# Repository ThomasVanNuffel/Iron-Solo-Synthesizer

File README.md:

# Main Directory
This repository is about the two phases of the project.

First phase: Practise Enterprise 1

    - XC888-DIL (microcontroller)
    - Input matrix with keys from keyboard
    - Led matrix
    - Serial interface with signal generators (with chip selector)

Second phase: Practise Enterprise 2

    - STM32F7508-DK (microcontroller)
    - Better serial interface with more signal generators
    - Communication with XC888 (to have all features of previous year)
    - MIDI communication
    - Hardware audio effects:
        - Envelopes
        - Low pass filter
        - High pas filter

    - Line input with small mixing stage

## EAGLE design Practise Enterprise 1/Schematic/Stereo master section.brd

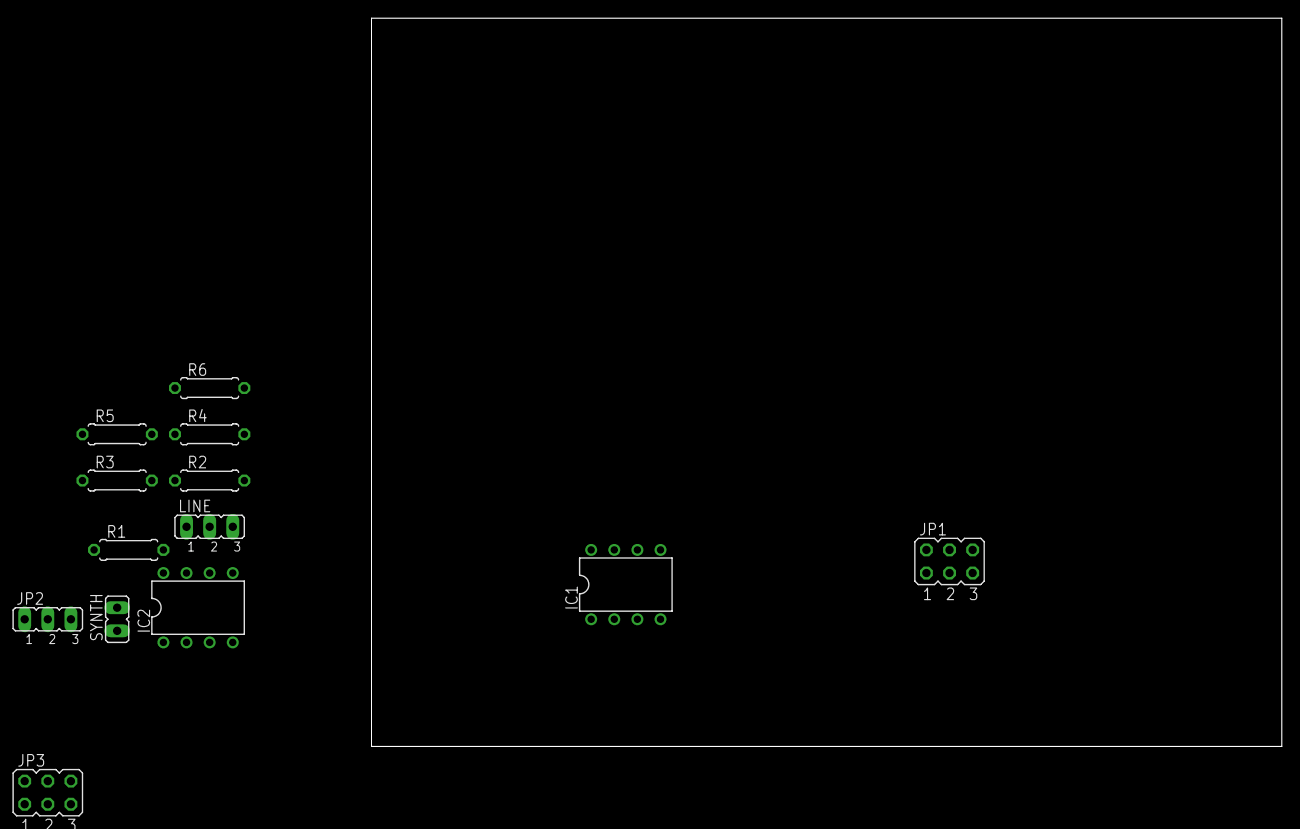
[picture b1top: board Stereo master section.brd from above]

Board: 2 copper layers, 100.0 x 80.0 mm, 13 parts (0 on the bottom side), 13 nets, no tracks yet.

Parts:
IC1, IC2: LM358N; DIL08
JP1, JP3: JP3Q
JP2: JP2
LINE: JP2
R1, R2, R5, R6: 1k; 0207/7
R3, R4: 5k; 0207/7
SYNTH: JP1

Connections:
unnamed: R3.1, R4.1, SYNTH.2
unnamed: IC1.2, R1.1, R3.2
unnamed: IC2.6, JP1.3, R5.2
unnamed: IC1.6, R2.1, R4.2
unnamed: IC1.7, LINE.2, R2.2, R5.1
unnamed: IC2.2, JP1.4, R6.2
unnamed: LINE.3, R6.1
unnamed: IC2.7, JP1.5
unnamed: IC2.1, JP1.6
unnamed: IC1.8, IC2.8, JP2.3
unnamed: IC1.4, IC2.4, JP2.2
unnamed: IC1.3, IC1.5, IC2.3, IC2.5, JP1.1, JP1.2, JP2.1, SYNTH.1
unnamed: IC1.1, R1.2

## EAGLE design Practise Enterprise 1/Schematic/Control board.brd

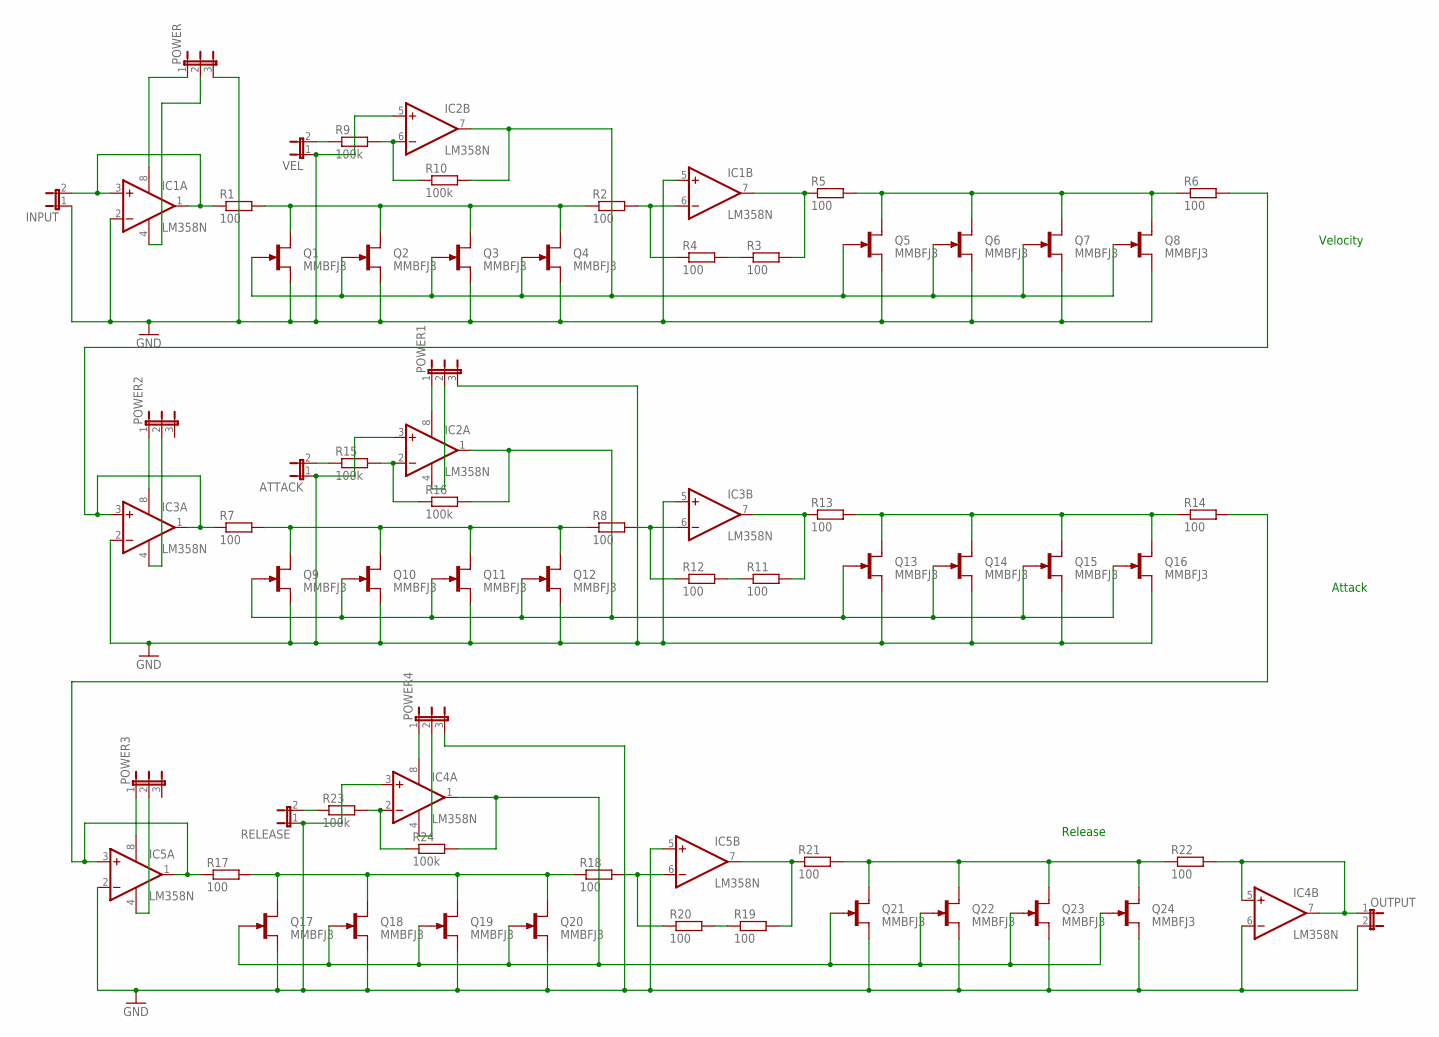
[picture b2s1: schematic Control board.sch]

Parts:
ATTACK: JP1E; JP1
IC1, IC2, IC3, IC4, IC5: LM358N; DIL08
INPUT: JP1E; JP1
OUTPUT: JP1E; JP1
POWER, POWER1, POWER2, POWER3, POWER4: JP2E; JP2
Q1, Q2, Q3, Q4, Q5, Q6, Q7, Q8, Q9, Q10, Q11, Q12, Q13, Q14, Q15, Q16, Q17, Q18, Q19, Q20, Q21, Q22, Q23, Q24: MMBFJ3; SOT23
R1, R2, R3, R4, R5, R6, R7, R8, R11, R12, R13, R14, R17, R18, R19, R20, R21, R22: 100; 0204/7
R9, R10, R15, R16, R23, R24: 100k; 0204/7
RELEASE: JP1E; JP1
VEL: JP1E; JP1

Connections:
22: Q13.1 (D), Q14.1 (D), Q15.1 (D), Q16.1 (D), R13.2, R14.1
CONTROL: IC2.7 (OUT), Q1.3 (G), Q2.3 (G), Q3.3 (G), Q4.3 (G), Q5.3 (G), Q6.3 (G), Q7.3 (G), Q8.3 (G), R10.2
CONTROL1: IC2.1 (OUT), Q9.3 (G), Q10.3 (G), Q11.3 (G), Q12.3 (G), Q13.3 (G), Q14.3 (G), Q15.3 (G), Q16.3 (G), R16.2
CONTROL2: IC4.1 (OUT), Q17.3 (G), Q18.3 (G), Q19.3 (G), Q20.3 (G), Q21.3 (G), Q22.3 (G), Q23.3 (G), Q24.3 (G), R24.2
GND: ATTACK.1, IC1.2 (-IN), IC1.5 (+IN), IC2.3 (+IN), IC2.5 (+IN), IC3.2 (-IN), IC3.5 (+IN), IC4.3 (+IN), IC4.6 (-IN), IC5.2 (-IN), IC5.5 (+IN), INPUT.1, OUTPUT.2, POWER.3, POWER1.3, POWER4.3, Q1.2 (S), Q2.2 (S), Q3.2 (S), Q4.2 (S), Q5.2 (S), Q6.2 (S), Q7.2 (S), Q8.2 (S), Q9.2 (S), Q10.2 (S), Q11.2 (S), Q12.2 (S), Q13.2 (S), Q14.2 (S), Q15.2 (S), Q16.2 (S), Q17.2 (S), Q18.2 (S), Q19.2 (S), Q20.2 (S), Q21.2 (S), Q22.2 (S), Q23.2 (S), Q24.2 (S), RELEASE.1, VEL.1
unnamed: IC4.8 (V+), POWER4.1
unnamed: IC1.8 (V+), POWER.1
unnamed: IC1.6 (-IN), R2.2, R4.1
unnamed: IC1.1 (OUT), IC1.3 (+IN), INPUT.2, R1.1
unnamed: R3.1, R4.2
unnamed: IC4.4 (V-), POWER4.2
unnamed: IC1.7 (OUT), R3.2, R5.1
unnamed: R9.1, VEL.2
unnamed: IC3.1 (OUT), IC3.3 (+IN), R6.2, R7.1
unnamed: IC5.8 (V+), POWER3.1
unnamed: IC2.6 (-IN), R9.2, R10.1
unnamed: IC4.5 (+IN), IC4.7 (OUT), OUTPUT.1, R22.2
unnamed: IC5.4 (V-), POWER3.2
unnamed: IC3.6 (-IN), R8.2, R12.1
unnamed: R11.1, R12.2
unnamed: IC3.7 (OUT), R11.2, R13.1
unnamed: IC3.8 (V+), POWER2.1
unnamed: IC5.1 (OUT), IC5.3 (+IN), R14.2, R17.1
unnamed: ATTACK.2, R15.1
unnamed: IC2.2 (-IN), R15.2, R16.1
unnamed: IC3.4 (V-), POWER2.2
unnamed: IC2.8 (V+), POWER1.1
unnamed: IC1.4 (V-), POWER.2
unnamed: IC2.4 (V-), POWER1.2
unnamed: IC5.6 (-IN), R18.2, R20.1
unnamed: R19.1, R20.2
unnamed: IC5.7 (OUT), R19.2, R21.1
unnamed: R23.1, RELEASE.2
unnamed: IC4.2 (-IN), R23.2, R24.1
NET11: Q1.1 (D), Q2.1 (D), Q3.1 (D), Q4.1 (D), R1.2, R2.1
NET12: Q5.1 (D), Q6.1 (D), Q7.1 (D), Q8.1 (D), R5.2, R6.1
NET21: Q9.1 (D), Q10.1 (D), Q11.1 (D), Q12.1 (D), R7.2, R8.1
NET31: Q17.1 (D), Q18.1 (D), Q19.1 (D), Q20.1 (D), R17.2, R18.1
NET32: Q21.1 (D), Q22.1 (D), Q23.1 (D), Q24.1 (D), R21.2, R22.1

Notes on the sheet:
Velocity
Attack
Release

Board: 2 copper layers, 63 parts (0 on the bottom side), 39 nets, no tracks yet.

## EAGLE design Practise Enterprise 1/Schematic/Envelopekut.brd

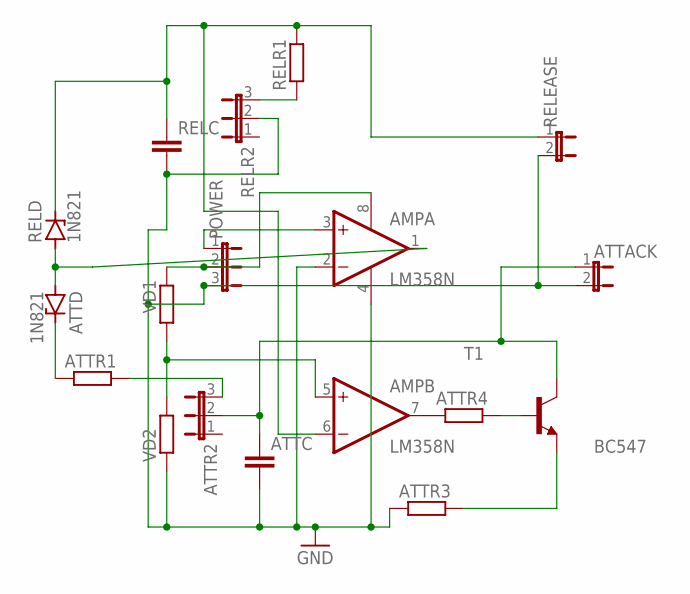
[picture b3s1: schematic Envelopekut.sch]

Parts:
AMP: LM358N; DIL08
ATTACK: JP1E; JP1
ATTC: C-EU025-025X050; C025-025X050
ATTD: 1N821; DO35Z10
ATTR1, ATTR3, ATTR4: R-EU_0207/10; 0207/10
ATTR2: JP2E; JP2
POWER: JP2E; JP2
RELC: C-EU025-025X050; C025-025X050
RELD: 1N821; DO35Z10
RELEASE: JP1E; JP1
RELR1: R-EU_0207/10; 0207/10
RELR2: JP2E; JP2
T1: BC547; TO92
VD1, VD2: R-EU_0207/10; 0207/10

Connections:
GND: AMP.2 (-IN), AMP.4 (V-), ATTACK.2, ATTC.2, ATTR3.1, POWER.3, RELC.2, RELEASE.2, RELR2.2, VD2.1
unnamed: AMP.5 (+IN), VD1.1, VD2.2
unnamed: AMP.7 (OUT), ATTR4.1
unnamed: ATTR4.2, T1.2 (B)
unnamed: ATTR1.2, ATTR2.3
unnamed: ATTR3.2, T1.1 (E)
unnamed: ATTACK.1, ATTC.1, ATTR2.2, T1.3 (C)
unnamed: ATTD.C, ATTR1.1
unnamed: AMP.1 (OUT), ATTD.A, RELD.A
unnamed: AMP.8 (V+), POWER.2, VD1.2
unnamed: AMP.3 (+IN), POWER.1
unnamed: AMP.6 (-IN), RELC.1, RELD.C, RELEASE.1, RELR1.2
unnamed: RELR1.1, RELR2.3

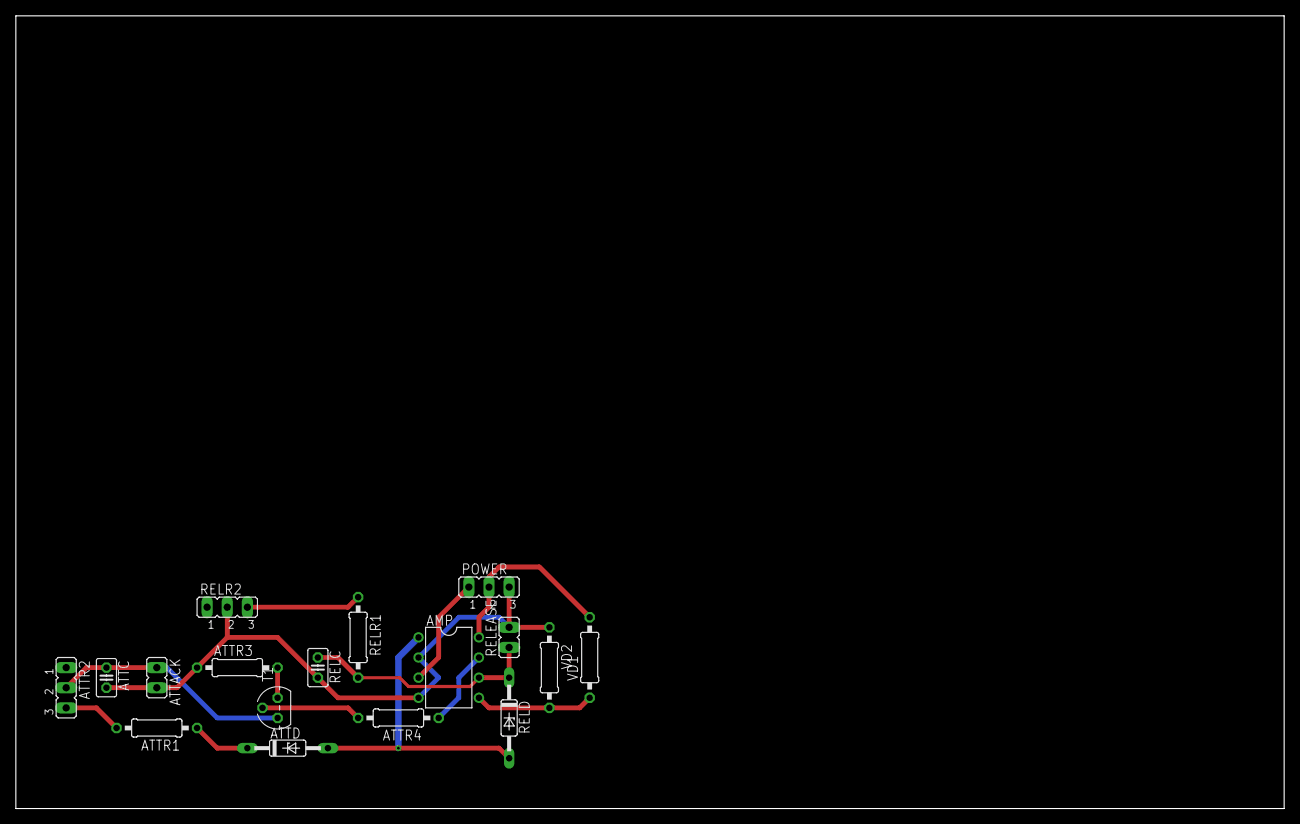
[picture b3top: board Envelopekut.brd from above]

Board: 2 copper layers, 160.0 x 100.0 mm, 17 parts (0 on the bottom side), 13 nets.

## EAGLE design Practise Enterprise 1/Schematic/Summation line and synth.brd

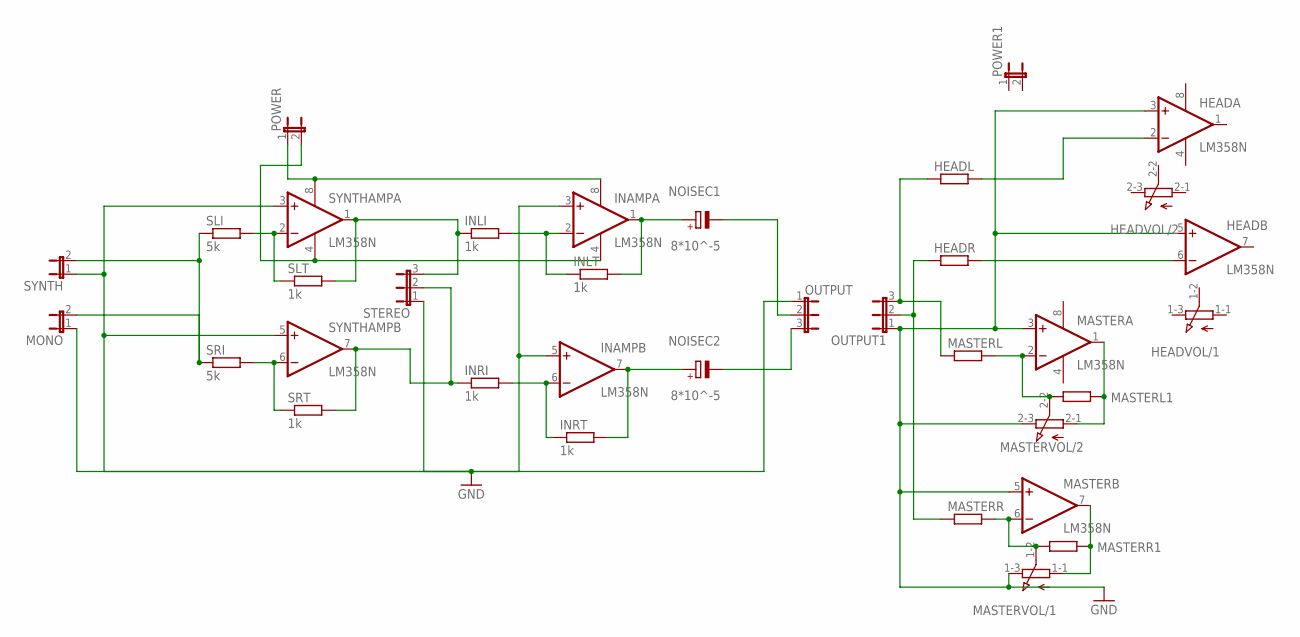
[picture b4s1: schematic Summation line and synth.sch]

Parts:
HEAD: LM358N; DIL08
HEADL: R-EU_0207/7; 0207/7
HEADR: R-EU_0207/7; 0207/7
HEADVOL: 3RP/1610G
INAMP: LM358N; DIL08
INLI: 1k; 0207/7
INLT: 1k; 0207/7
INRI: 1k; 0207/7
INRT: 1k; 0207/7
MASTER: LM358N; DIL08
MASTERL, MASTERL1: R-EU_0207/7; 0207/7
MASTERR, MASTERR1: R-EU_0207/7; 0207/7
MASTERVOL: 3RP/1610G
MONO: JP1E; JP1
NOISEC1, NOISEC2: 8*10^-5; E5-5
OUTPUT, OUTPUT1: JP2E; JP2
POWER, POWER1: JP1E; JP1
SLI: 5k; 0207/7
SLT: 1k; 0207/7
SRI: 5k; 0207/7
SRT: 1k; 0207/7
STEREO: JP2E; JP2
SYNTH: JP1E; JP1
SYNTHAMP: LM358N; DIL08

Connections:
GND: HEAD.3 (+IN), HEAD.5 (+IN), INAMP.3 (+IN), INAMP.5 (+IN), MASTER.3 (+IN), MASTER.5 (+IN), MASTERVOL.1-3 (E), MASTERVOL.2-3 (E), MONO.1, OUTPUT.1, OUTPUT1.1, STEREO.1, SYNTH.1, SYNTHAMP.3 (+IN), SYNTHAMP.5 (+IN)
unnamed: INAMP.4 (V-), POWER.2, SYNTHAMP.4 (V-)
unnamed: SLI.2, SLT.1, SYNTHAMP.2 (-IN)
unnamed: INAMP.6 (-IN), INRI.2, INRT.1
unnamed: SRI.2, SRT.1, SYNTHAMP.6 (-IN)
unnamed: INRI.1, SRT.2, STEREO.2, SYNTHAMP.7 (OUT)
unnamed: INAMP.2 (-IN), INLI.2, INLT.1
unnamed: INAMP.8 (V+), POWER.1, SYNTHAMP.8 (V+)
unnamed: INLI.1, SLT.2, STEREO.3, SYNTHAMP.1 (OUT)
unnamed: INAMP.7 (OUT), INRT.2, NOISEC2.+
unnamed: INAMP.1 (OUT), INLT.2, NOISEC1.+
unnamed: NOISEC1.-, OUTPUT.2
unnamed: NOISEC2.-, OUTPUT.3
unnamed: MASTER.2 (-IN), MASTERL.2, MASTERL1.1, MASTERVOL.2-2 (S)
unnamed: HEADL.1, MASTERL.1, OUTPUT1.3
unnamed: HEAD.2 (-IN), HEADL.2
unnamed: HEAD.6 (-IN), HEADR.2
unnamed: HEADR.1, MASTERR.1, OUTPUT1.2
unnamed: MASTER.6 (-IN), MASTERR.2, MASTERR1.1, MASTERVOL.1-2 (S)
unnamed: MASTER.7 (OUT), MASTERR1.2, MASTERVOL.1-1 (A)
unnamed: MASTER.1 (OUT), MASTERL1.2, MASTERVOL.2-1 (A)
SYNTHIN: MONO.2, SLI.1, SRI.1, SYNTH.2
V+: HEAD.8 (V+), MASTER.8 (V+)
V-: HEAD.4 (V-), MASTER.4 (V-)

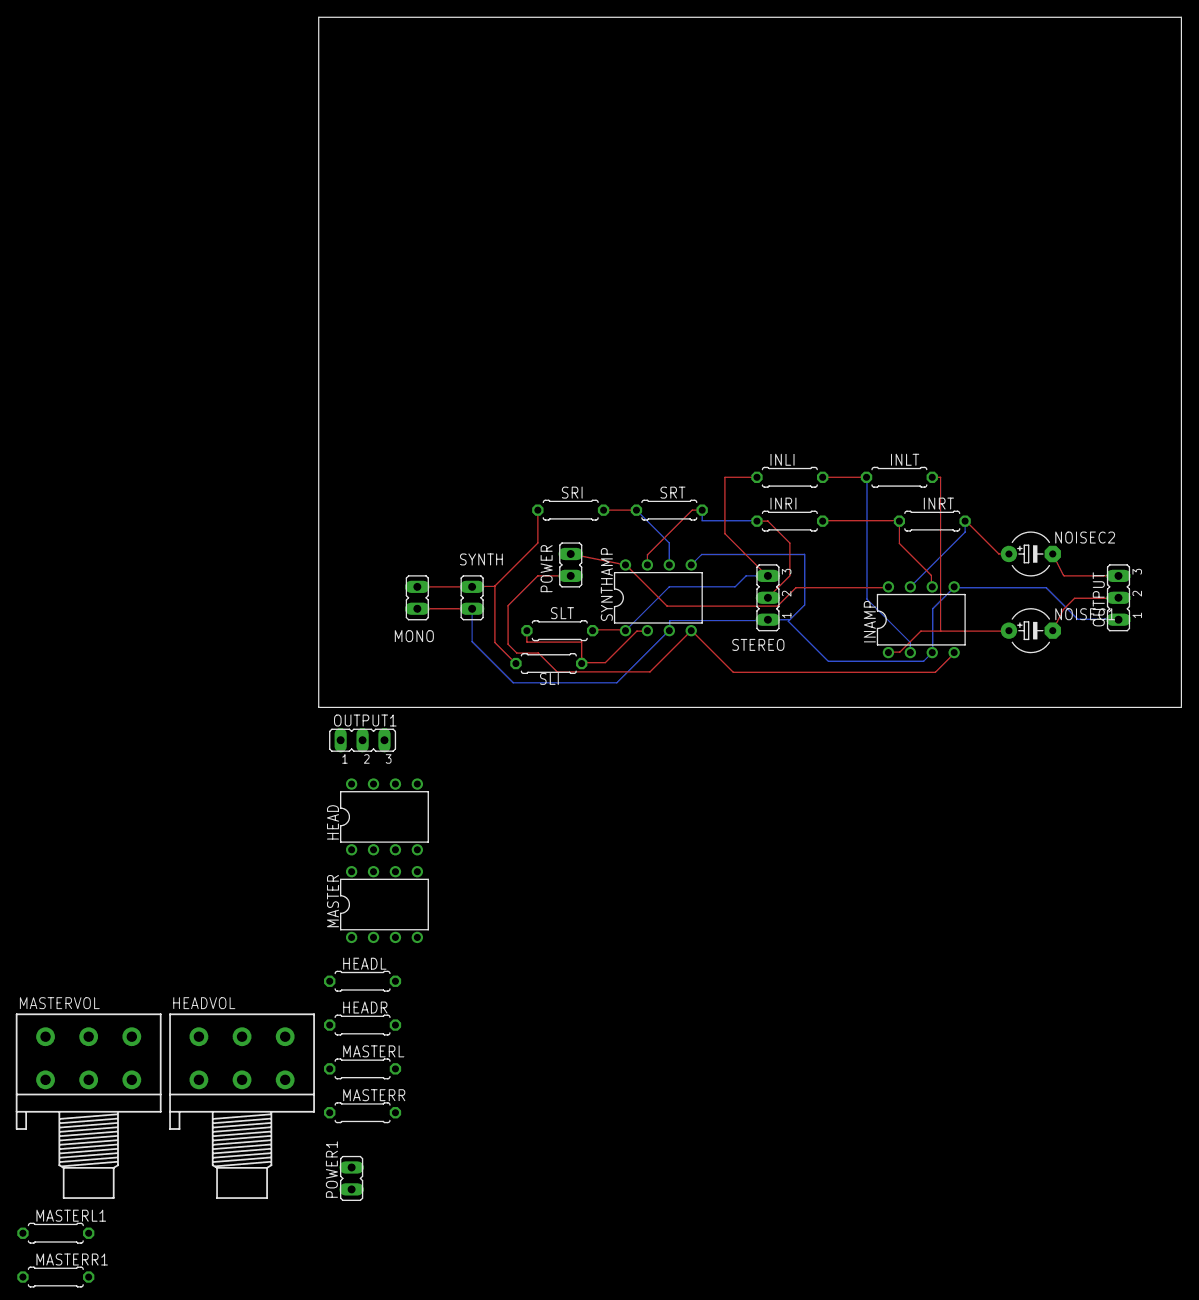
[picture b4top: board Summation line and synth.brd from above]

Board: 2 copper layers, 100.0 x 80.0 mm, 29 parts (0 on the bottom side), 24 nets.

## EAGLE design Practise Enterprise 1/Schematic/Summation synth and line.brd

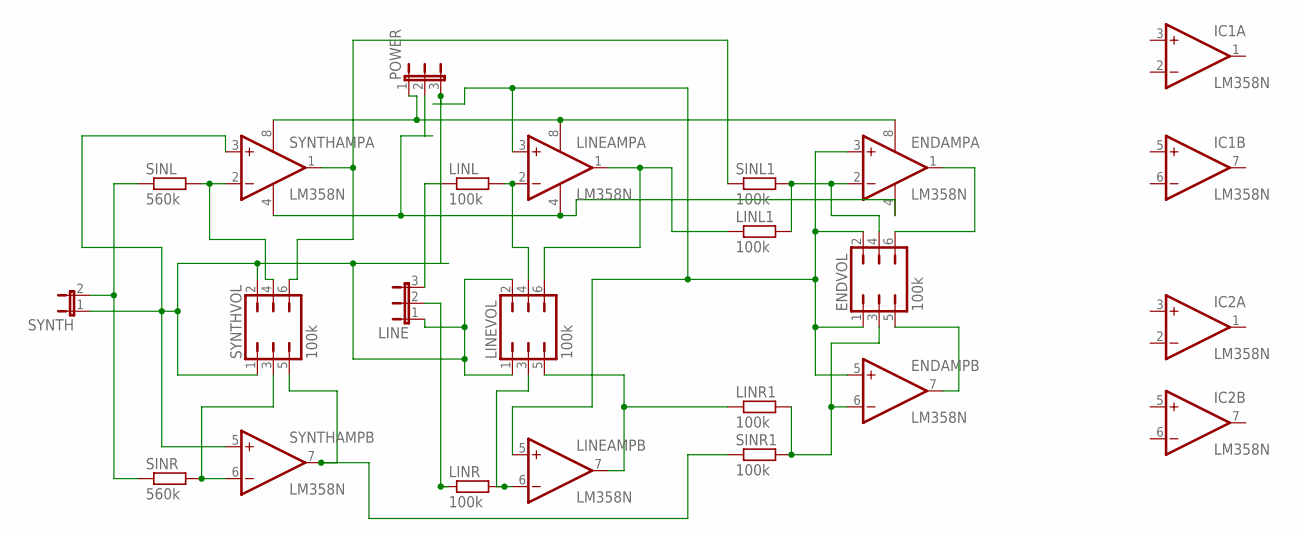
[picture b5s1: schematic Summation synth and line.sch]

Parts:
ENDAMP: LM358N; DIL08
ENDVOL: 100k; JP3Q
IC1, IC2: LM358N; DIL08
LINE: JP2E; JP2
LINEAMP: LM358N; DIL08
LINEVOL: 100k; JP3Q
LINL, LINL1: 100k; 0207/7
LINR, LINR1: 100k; 0207/7
POWER: JP2E; JP2
SINL: 560k; 0207/7
SINL1: 100k; 0207/7
SINR: 560k; 0207/7
SINR1: 100k; 0207/7
SYNTH: JP1E; JP1
SYNTHAMP: LM358N; DIL08
SYNTHVOL: 100k; JP3Q

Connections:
unnamed: LINE.3, LINL.1
unnamed: SINL.2, SYNTHAMP.2 (-IN), SYNTHVOL.4
unnamed: SINL.1, SINR.1, SYNTH.2
unnamed: LINEAMP.2 (-IN), LINEVOL.4, LINL.2
unnamed: SINR.2, SYNTHAMP.6 (-IN), SYNTHVOL.3
unnamed: SINR1.1, SYNTHAMP.7 (OUT), SYNTHVOL.5
unnamed: LINE.2, LINR.1
unnamed: LINEAMP.6 (-IN), LINEVOL.3, LINR.2
unnamed: LINEAMP.1 (OUT), LINEVOL.6, LINL1.1
unnamed: SINL1.1, SYNTHAMP.1 (OUT), SYNTHVOL.6
unnamed: ENDAMP.6 (-IN), ENDVOL.3, LINR1.2, SINR1.2
unnamed: LINEAMP.7 (OUT), LINEVOL.5, LINR1.1
unnamed: ENDAMP.8 (V+), LINEAMP.8 (V+), POWER.1, SYNTHAMP.8 (V+)
unnamed: ENDAMP.4 (V-), LINEAMP.4 (V-), POWER.2, SYNTHAMP.4 (V-)
unnamed: ENDAMP.3 (+IN), ENDAMP.5 (+IN), ENDVOL.1, ENDVOL.2, LINE.1, LINEAMP.3 (+IN), LINEAMP.5 (+IN), LINEVOL.1, LINEVOL.2, POWER.3, SYNTH.1, SYNTHAMP.3 (+IN), SYNTHAMP.5 (+IN), SYNTHVOL.1, SYNTHVOL.2
unnamed: ENDAMP.2 (-IN), ENDVOL.4, LINL1.2, SINL1.2
unnamed: ENDAMP.1 (OUT), ENDVOL.6
unnamed: ENDAMP.7 (OUT), ENDVOL.5
V+: IC1.8 (V+), IC2.8 (V+)
V-: IC1.4 (V-), IC2.4 (V-)

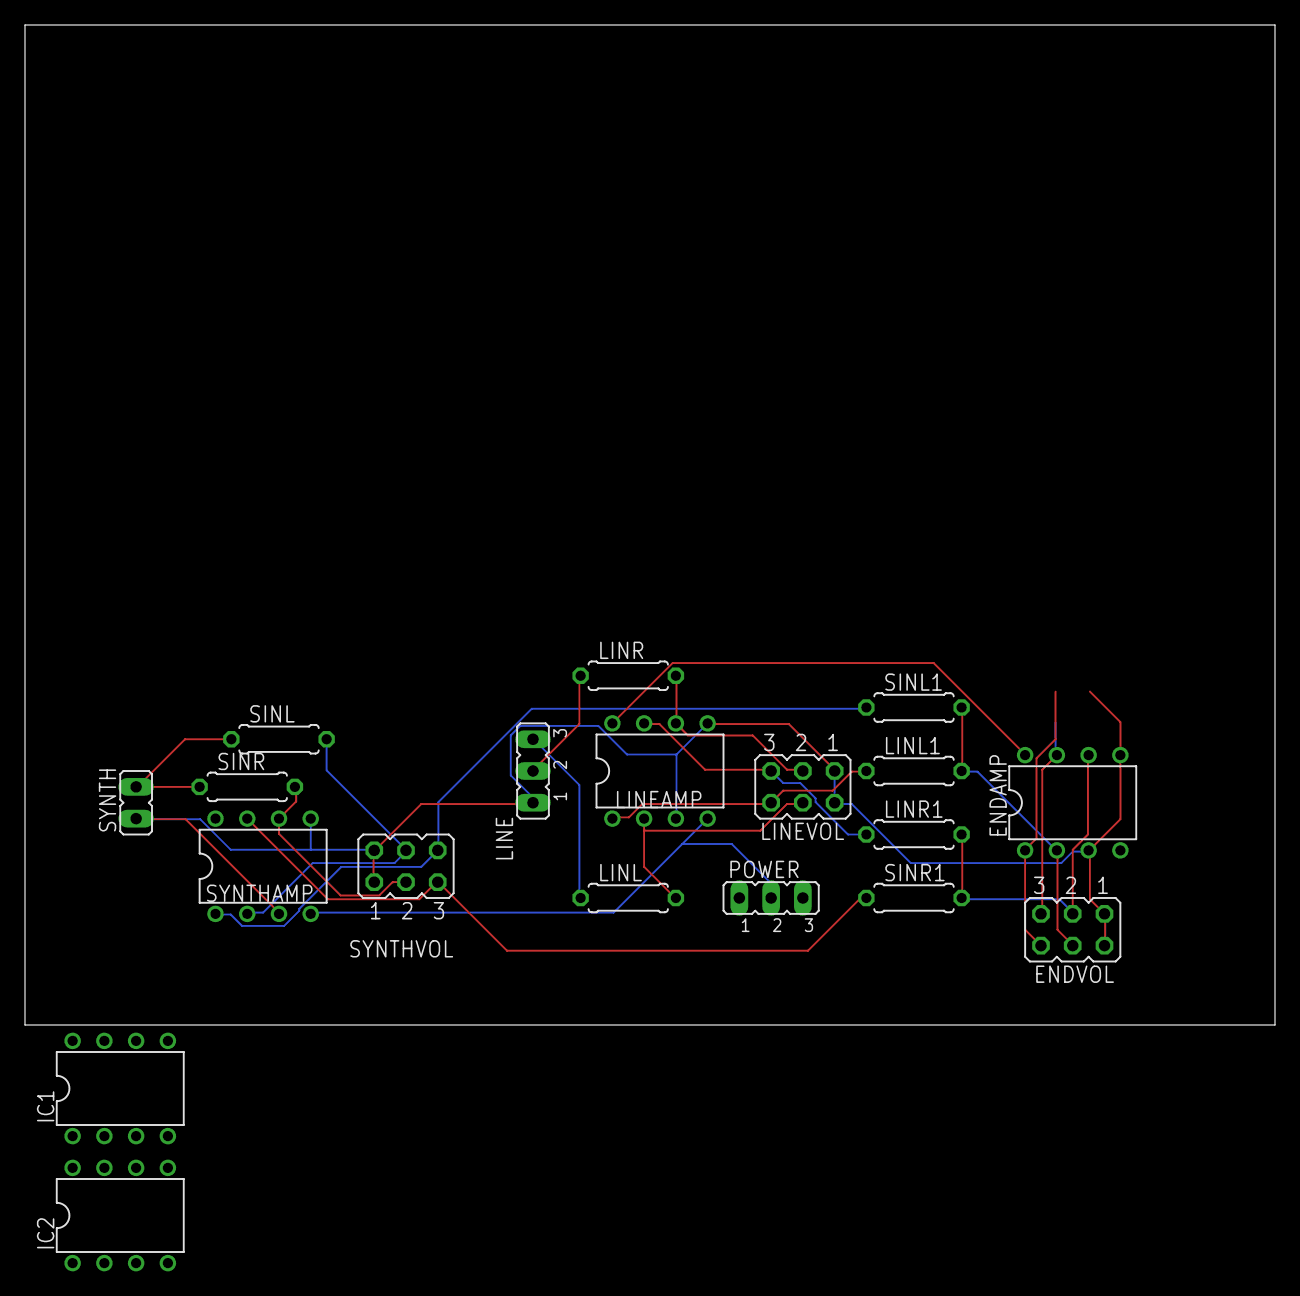
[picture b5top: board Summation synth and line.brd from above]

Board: 2 copper layers, 100.0 x 80.0 mm, 19 parts (0 on the bottom side), 20 nets.

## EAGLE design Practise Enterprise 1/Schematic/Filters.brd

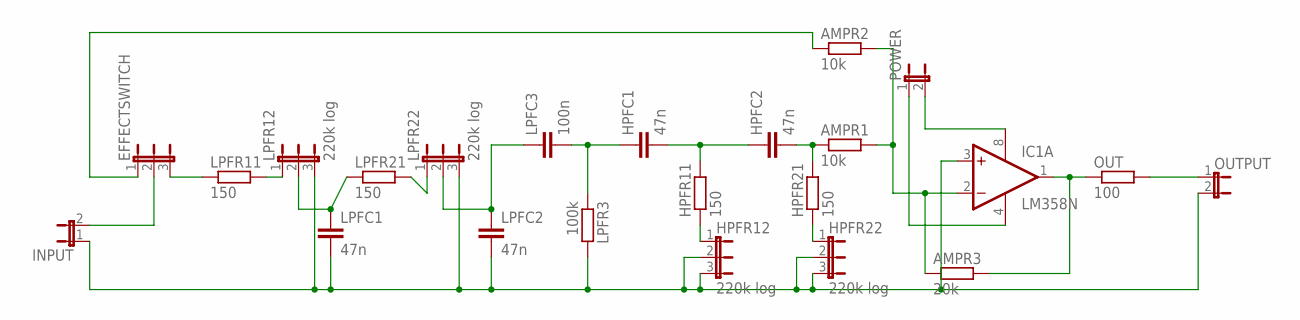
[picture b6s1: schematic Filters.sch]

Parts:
AMPR1, AMPR2: 10k; 0207/10
AMPR3: 20k; 0207/10
EFFECTSWITCH: 220k log; JP2
HPFC1, HPFC2: 47n; C025-025X050
HPFR11, HPFR21: 150; 0207/10
HPFR12, HPFR22: 220k log; JP2
IC1: LM358N; DIL08
INPUT: JP1E; JP1
LPFC1, LPFC2: 47n; C025-025X050
LPFC3: 100n; C025-025X050
LPFR3: 100k; 0207/10
LPFR11, LPFR21: 150; 0207/10
LPFR12, LPFR22: 220k log; JP2
OUT: 100; 0207/10
OUTPUT: JP1E; JP1
POWER: JP1E; JP1

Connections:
unnamed: LPFR11.2, LPFR12.1
unnamed: LPFC1.1, LPFR12.2, LPFR21.1
unnamed: LPFC2.1, LPFC3.1, LPFR22.2
unnamed: HPFR12.2, HPFR12.3, HPFR22.2, HPFR22.3, IC1.3 (+IN), INPUT.1, LPFC1.2, LPFC2.2, LPFR3.2, LPFR12.3, LPFR22.3, OUTPUT.2
unnamed: EFFECTSWITCH.3, LPFR11.1
unnamed: HPFC1.2, HPFC2.1, HPFR11.2
unnamed: AMPR3.2, IC1.1 (OUT), OUT.1
unnamed: IC1.8 (V+), POWER.2
unnamed: IC1.4 (V-), POWER.1
unnamed: OUT.2, OUTPUT.1
unnamed: AMPR2.1, EFFECTSWITCH.1
unnamed: LPFR21.2, LPFR22.1
unnamed: HPFR21.1, HPFR22.1
unnamed: AMPR1.1, HPFC2.2, HPFR21.2
unnamed: HPFR11.1, HPFR12.1
unnamed: HPFC1.1, LPFC3.2, LPFR3.1
unnamed: EFFECTSWITCH.2, INPUT.2
unnamed: AMPR1.2, AMPR2.2, AMPR3.1, IC1.2 (-IN)

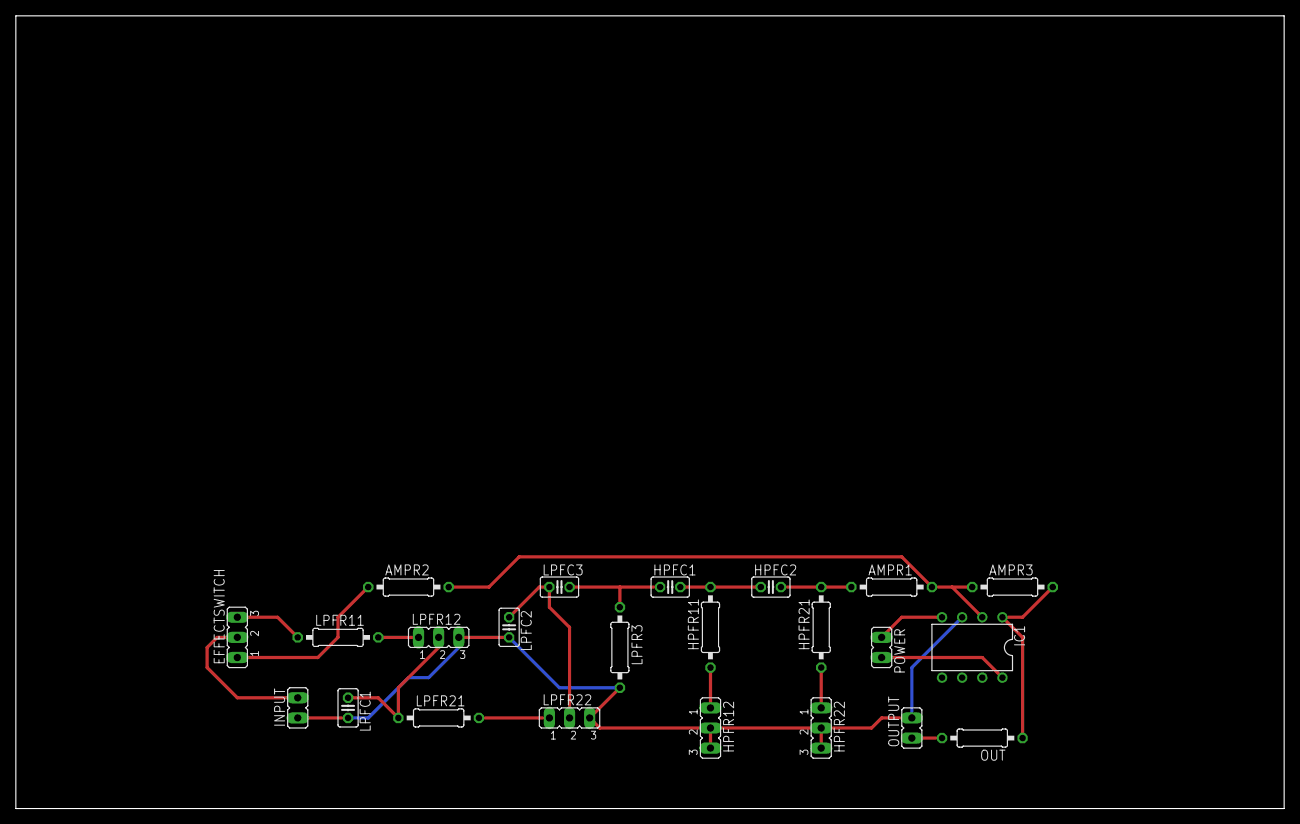
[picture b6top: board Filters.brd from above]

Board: 2 copper layers, 160.0 x 100.0 mm, 23 parts (0 on the bottom side), 18 nets.

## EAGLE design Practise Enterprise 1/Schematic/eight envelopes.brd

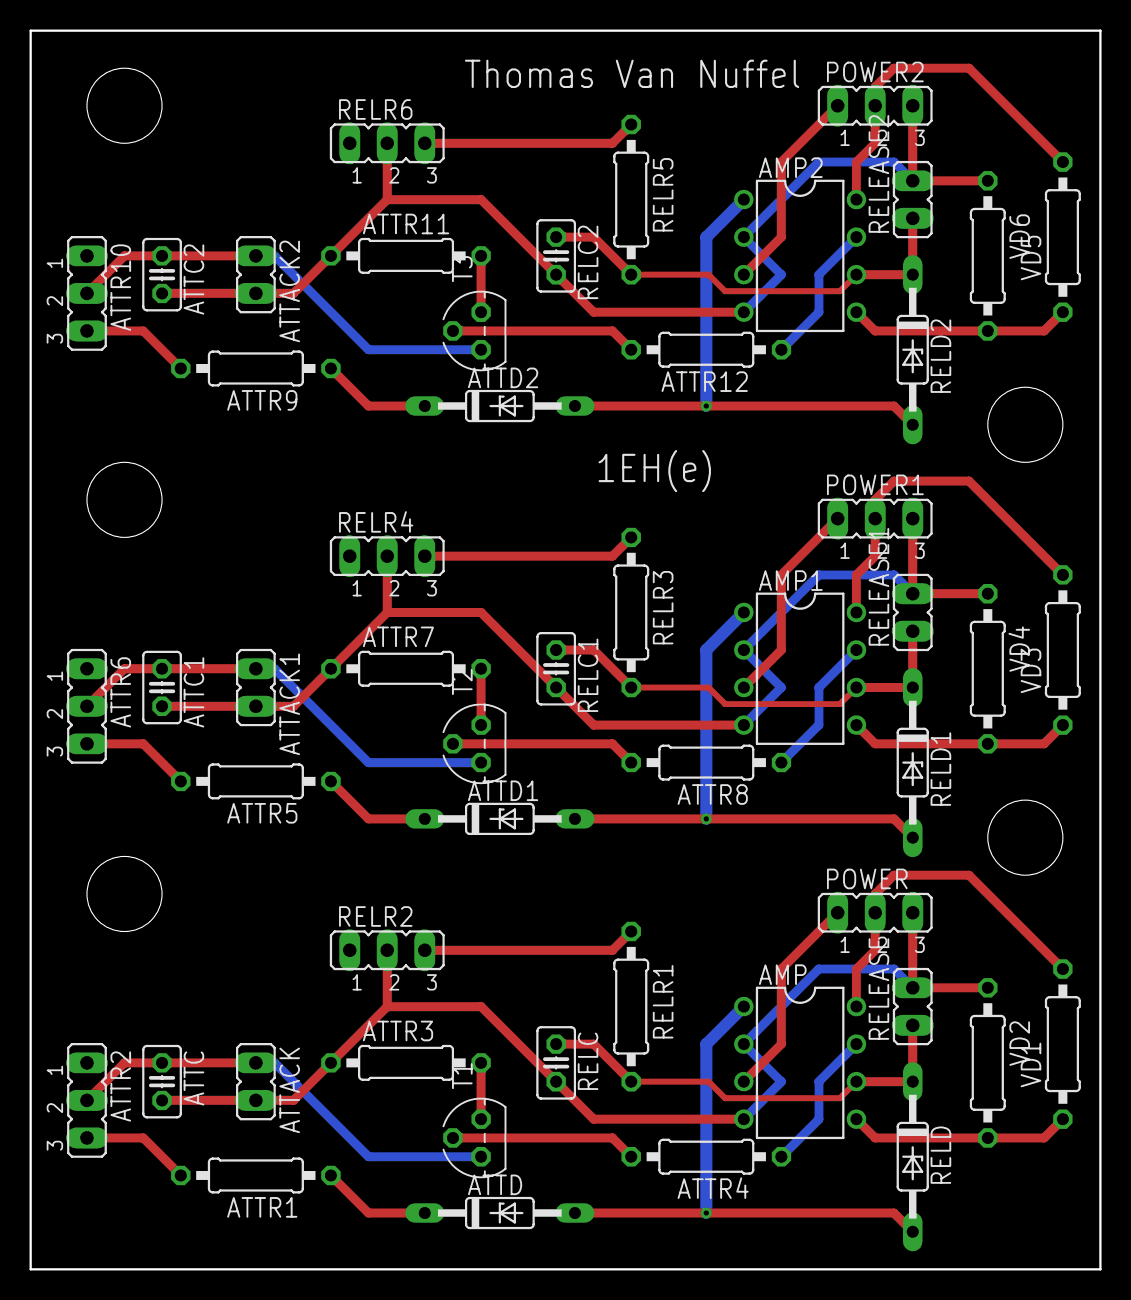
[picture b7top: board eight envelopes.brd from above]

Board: 2 copper layers, 72.4 x 83.8 mm, 51 parts (0 on the bottom side), 39 nets.

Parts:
AMP, AMP1, AMP2: LM358N; DIL08
ATTACK, ATTACK1, ATTACK2: JP1
ATTC, ATTC1, ATTC2: C025-025X050
ATTD, ATTD1, ATTD2: 1N821; DO35Z10
ATTR1, ATTR3, ATTR4, ATTR5, ATTR7, ATTR8, ATTR9, ATTR11, ATTR12: 0207/10
ATTR2, ATTR6, ATTR10: JP2
POWER, POWER1, POWER2: JP2
RELC, RELC1, RELC2: C025-025X050
RELD, RELD1, RELD2: 1N821; DO35Z10
RELEASE, RELEASE1, RELEASE2: JP1
RELR1, RELR3, RELR5: 0207/10
RELR2, RELR4, RELR6: JP2
T1, T2, T3: BC547; TO92
VD1, VD2, VD3, VD4, VD5, VD6: 0207/10

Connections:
GND: AMP.2, AMP.4, ATTACK.2, ATTC.2, ATTR3.1, POWER.3, RELC.2, RELEASE.2, RELR2.2, VD2.1
GND1: AMP1.2, AMP1.4, ATTACK1.2, ATTC1.2, ATTR7.1, POWER1.3, RELC1.2, RELEASE1.2, RELR4.2, VD4.1
GND2: AMP2.2, AMP2.4, ATTACK2.2, ATTC2.2, ATTR11.1, POWER2.3, RELC2.2, RELEASE2.2, RELR6.2, VD6.1
unnamed: AMP.5, VD1.1, VD2.2
unnamed: AMP.7, ATTR4.1
unnamed: ATTR4.2, T1.2
unnamed: ATTR1.2, ATTR2.3
unnamed: ATTR3.2, T1.1
unnamed: ATTACK.1, ATTC.1, ATTR2.2, T1.3
unnamed: ATTD.C, ATTR1.1
unnamed: AMP.1, ATTD.A, RELD.A
unnamed: AMP.8, POWER.2, VD1.2
unnamed: AMP.3, POWER.1
unnamed: AMP.6, RELC.1, RELD.C, RELEASE.1, RELR1.2
unnamed: RELR1.1, RELR2.3
unnamed: AMP1.5, VD3.1, VD4.2
unnamed: AMP1.7, ATTR8.1
unnamed: ATTR8.2, T2.2
unnamed: ATTR7.2, T2.1
unnamed: ATTACK1.1, ATTC1.1, ATTR6.2, T2.3
unnamed: ATTD1.C, ATTR5.1
unnamed: ATTR5.2, ATTR6.3
unnamed: AMP1.1, ATTD1.A, RELD1.A
unnamed: AMP1.8, POWER1.2, VD3.2
unnamed: AMP1.6, RELC1.1, RELD1.C, RELEASE1.1, RELR3.2
unnamed: AMP1.3, POWER1.1
unnamed: RELR3.1, RELR4.3
unnamed: AMP2.5, VD5.1, VD6.2
unnamed: AMP2.7, ATTR12.1
unnamed: ATTR12.2, T3.2
unnamed: ATTR11.2, T3.1
unnamed: ATTACK2.1, ATTC2.1, ATTR10.2, T3.3
unnamed: ATTD2.C, ATTR9.1
unnamed: ATTR9.2, ATTR10.3
unnamed: AMP2.1, ATTD2.A, RELD2.A
unnamed: AMP2.8, POWER2.2, VD5.2
unnamed: AMP2.6, RELC2.1, RELD2.C, RELEASE2.1, RELR5.2
unnamed: AMP2.3, POWER2.1
unnamed: RELR5.1, RELR6.3

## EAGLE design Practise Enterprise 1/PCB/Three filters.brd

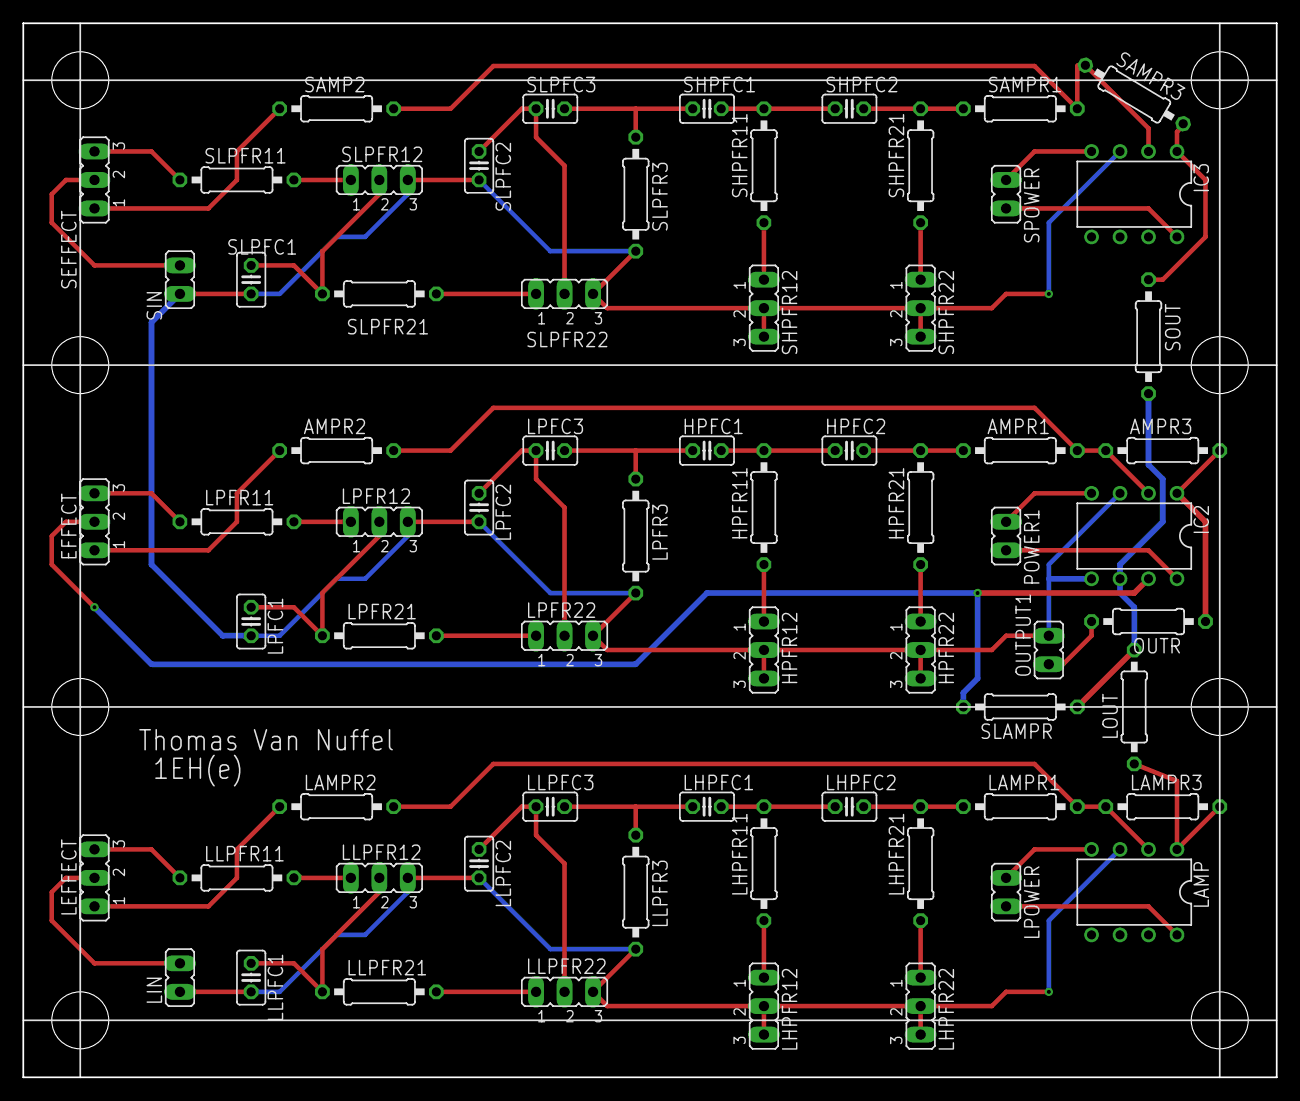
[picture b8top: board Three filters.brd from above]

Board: 2 copper layers, 111.8 x 94.0 mm, 67 parts (0 on the bottom side), 52 nets.

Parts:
AMPR1, AMPR2: 10k; 0207/10
AMPR3: 20k; 0207/10
EFFECT: 220k log; JP2
HPFC1, HPFC2: 47n; C025-025X050
HPFR11, HPFR21: 150; 0207/10
HPFR12, HPFR22: 220k log; JP2
IC2, IC3: LM358N; DIL08
LAMP: LM358N; DIL08
LAMPR1, LAMPR2: 10k; 0207/10
LAMPR3: 20k; 0207/10
LEFFECT: 220k log; JP2
LHPFC1, LHPFC2: 47n; C025-025X050
LHPFR11, LHPFR21: 150; 0207/10
LHPFR12, LHPFR22: 220k log; JP2
LIN: JP1
LLPFC1, LLPFC2: 47n; C025-025X050
LLPFC3: 100n; C025-025X050
LLPFR3: 100k; 0207/10
LLPFR11, LLPFR21: 150; 0207/10
LLPFR12, LLPFR22: 220k log; JP2
LOUT: 10k; 0207/10
LPFC1, LPFC2: 47n; C025-025X050
LPFC3: 100n; C025-025X050
LPFR3: 100k; 0207/10
LPFR11, LPFR21: 150; 0207/10
LPFR12, LPFR22: 220k log; JP2
LPOWER: JP1
OUTPUT1: JP1
OUTR: 100; 0207/10
POWER1: JP1
SAMP2: 10k; 0207/10
SAMPR1: 10k; 0207/10
SAMPR3: 20k; 0207/10
SEFFECT: 220k log; JP2
SHPFC1, SHPFC2: 47n; C025-025X050
SHPFR11, SHPFR21: 150; 0207/10
SHPFR12, SHPFR22: 220k log; JP2
SIN: JP1
SLAMPR: 10k; 0207/10
SLPFC1, SLPFC2: 47n; C025-025X050
SLPFC3: 100n; C025-025X050
SLPFR3: 100k; 0207/10
SLPFR11, SLPFR21: 150; 0207/10
SLPFR12, SLPFR22: 220k log; JP2
SOUT: 10k; 0207/10
SPOWER: JP1

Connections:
unnamed: LLPFR11.2, LLPFR12.1
unnamed: LLPFC1.1, LLPFR12.2, LLPFR21.1
unnamed: LLPFC2.1, LLPFC3.1, LLPFR22.2
unnamed: LAMP.3, LHPFR12.2, LHPFR12.3, LHPFR22.2, LHPFR22.3, LIN.1, LLPFC1.2, LLPFC2.2, LLPFR3.2, LLPFR12.3, LLPFR22.3
unnamed: LEFFECT.3, LLPFR11.1
unnamed: LHPFC1.2, LHPFC2.1, LHPFR11.2
unnamed: LPFR11.2, LPFR12.1
unnamed: LAMP.1, LAMPR3.2, LOUT.1
unnamed: LAMP.8, LPOWER.2
unnamed: LAMP.4, LPOWER.1
unnamed: LAMPR2.1, LEFFECT.1
unnamed: LLPFR21.2, LLPFR22.1
unnamed: LHPFR21.1, LHPFR22.1
unnamed: LAMPR1.1, LHPFC2.2, LHPFR21.2
unnamed: LHPFR11.1, LHPFR12.1
unnamed: LPFC1.1, LPFR12.2, LPFR21.1
unnamed: LPFC2.1, LPFC3.1, LPFR22.2
unnamed: LHPFC1.1, LLPFC3.2, LLPFR3.1
unnamed: LEFFECT.2, LIN.2
unnamed: LAMP.2, LAMPR1.2, LAMPR2.2, LAMPR3.1
unnamed: HPFC1.2, HPFC2.1, HPFR11.2
unnamed: IC2.8, POWER1.2
unnamed: IC2.4, POWER1.1
unnamed: OUTPUT1.1, OUTR.2
unnamed: LPFR21.2, LPFR22.1
unnamed: AMPR1.1, HPFC2.2, HPFR21.2
unnamed: HPFR21.1, HPFR22.1
unnamed: HPFR11.1, HPFR12.1
unnamed: HPFC1.1, LPFC3.2, LPFR3.1
unnamed: EFFECT.2, IC2.7, SLAMPR.2
unnamed: AMPR1.2, AMPR2.2, AMPR3.1, IC2.2
unnamed: AMPR2.1, EFFECT.1
unnamed: EFFECT.3, LPFR11.1
unnamed: SLPFR11.2, SLPFR12.1
unnamed: SLPFC1.1, SLPFR12.2, SLPFR21.1
unnamed: SLPFC2.1, SLPFC3.1, SLPFR22.2
unnamed: HPFR12.2, HPFR12.3, HPFR22.2, HPFR22.3, IC2.3, IC2.5, IC3.3, LPFC1.2, LPFC2.2, LPFR3.2, LPFR12.3, LPFR22.3, OUTPUT1.2, SHPFR12.2, SHPFR12.3, SHPFR22.2, SHPFR22.3, SIN.1, SLPFC1.2, SLPFC2.2, SLPFR3.2, SLPFR12.3, SLPFR22.3
unnamed: SHPFC1.2, SHPFC2.1, SHPFR11.2
unnamed: IC3.8, SPOWER.2
unnamed: IC3.4, SPOWER.1
unnamed: IC3.1, SAMPR3.2, SOUT.1
unnamed: SLPFR21.2, SLPFR22.1
unnamed: SAMPR1.1, SHPFC2.2, SHPFR21.2
unnamed: SHPFR21.1, SHPFR22.1
unnamed: SHPFR11.1, SHPFR12.1
unnamed: SHPFC1.1, SLPFC3.2, SLPFR3.1
unnamed: SEFFECT.2, SIN.2
unnamed: IC3.2, SAMP2.2, SAMPR1.2, SAMPR3.1
unnamed: SAMP2.1, SEFFECT.1
unnamed: SEFFECT.3, SLPFR11.1
S$1: IC2.6, LOUT.2, SLAMPR.1, SOUT.2
S$2: AMPR3.2, IC2.1, OUTR.1

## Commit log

2021-11-29 Adding PE1
